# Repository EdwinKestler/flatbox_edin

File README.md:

# flatbox_edin
Remote math inclusive education for the vision impaired

This is our first attempt to bring remote math edcuation to vision impaired persons. 

#IoT to empower humans. 

Hardware: Raspberry pi 4, 4GB Gateway paired via Wifi to Haptic interfase (drv2603) with response mechanism (MAX6817 de bounce) (vibration motors and push buttons) 2 units. 
IoT: JSON, MQTT, WiFi.
Software: Rabbit MQ, Node-Red, Maria DB, Node.js Angular 9
Cloud: Goolge cloud-> BigQuery, Pub/Sub, Cloud Functions (python and Node.js) 

Main Idea: so a teacher can remotely teach math  to many vision imparied studentes. 1 to many or 1 to 1, via the internet and aremote conference call
Techers interface:

Basic Hardware interface:

Licencing:

Software: 

Hardware: License: <tspan y="0" x="71.357224" id="tspan1179">CERN-OHL-1.2</tspan></text></g></g><text id="text1788" y="-45.219803" x="138.91757" style="font-style:normal;font-weight:normal;font-size:40.0001px;line-height:1.25;font-family:sans-serif;fill:#000000;fill-opacity:1;stroke:none;stroke-width:1" xml:space="preserve">
  
Documentation:

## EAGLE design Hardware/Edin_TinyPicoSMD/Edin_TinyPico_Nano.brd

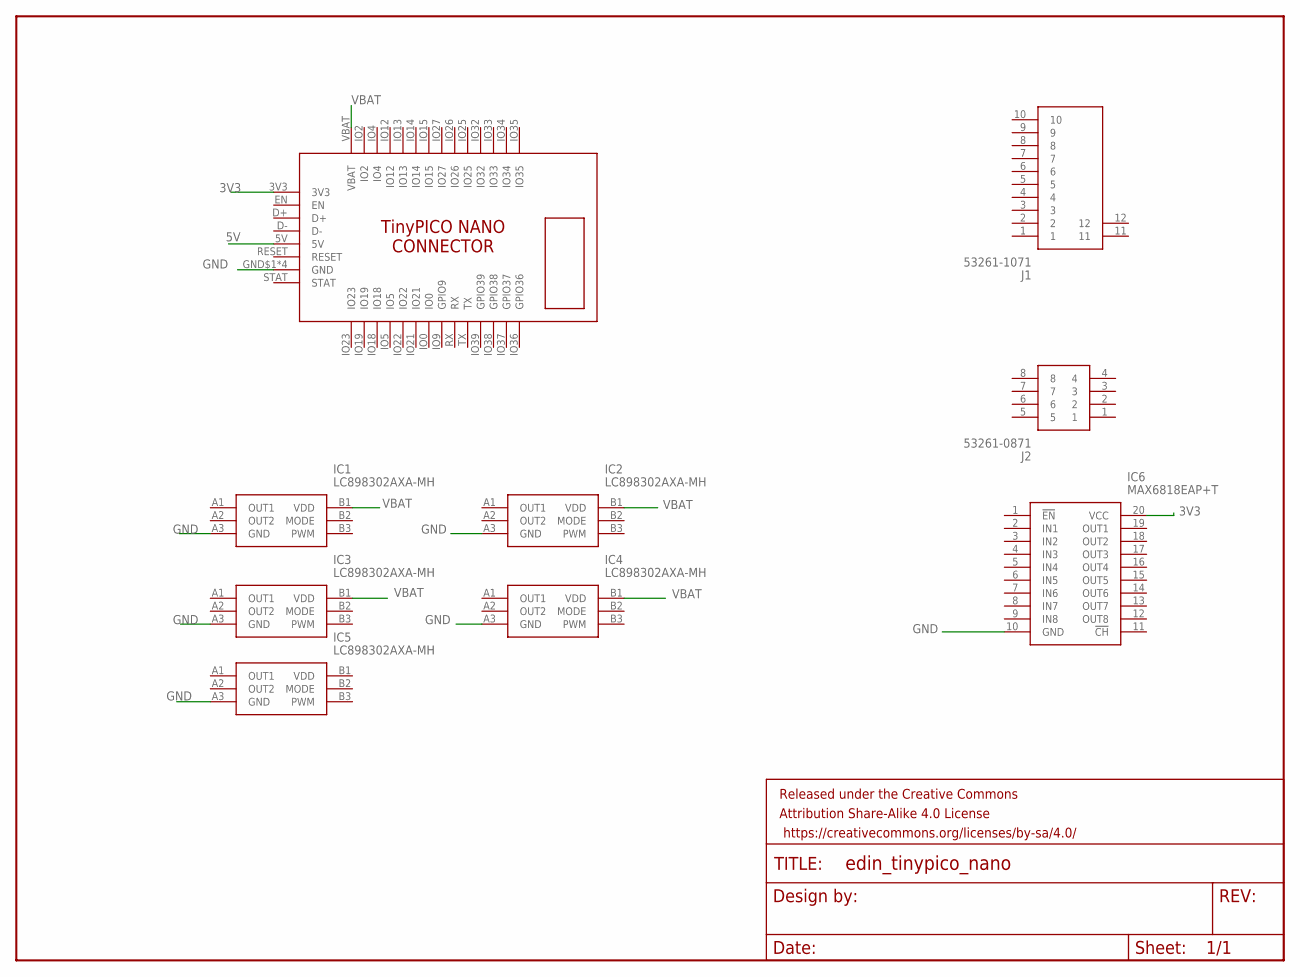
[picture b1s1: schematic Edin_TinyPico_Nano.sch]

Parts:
FRAME1: FRAME-LETTER; CREATIVE_COMMONS
IC1, IC2, IC3, IC4, IC5: LC898302AXA-MH; BGA6C40P3X2_118X78X65
IC6: MAX6818EAP+T; SOP65P778X199-20N
J1: 53261-1071; 532611071
J2: 53261-0871
U$1: TINYPICO-NANO-CONNECTOR

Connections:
3V3: IC6.20 (VCC), U$1.3V3
5V: U$1.5V
GND: IC1.A3 (GND), IC2.A3 (GND), IC3.A3 (GND), IC4.A3 (GND), IC5.A3 (GND), IC6.10 (GND), U$1.GND$1 (GND), U$1.GND$2 (GND), U$1.GND$3 (GND), U$1.GND$4 (GND)
VBAT: IC1.B1 (VDD), IC2.B1 (VDD), IC3.B1 (VDD), IC4.B1 (VDD), U$1.VBAT

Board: 2 copper layers, 10 parts (0 on the bottom side), 3 nets, no tracks yet.

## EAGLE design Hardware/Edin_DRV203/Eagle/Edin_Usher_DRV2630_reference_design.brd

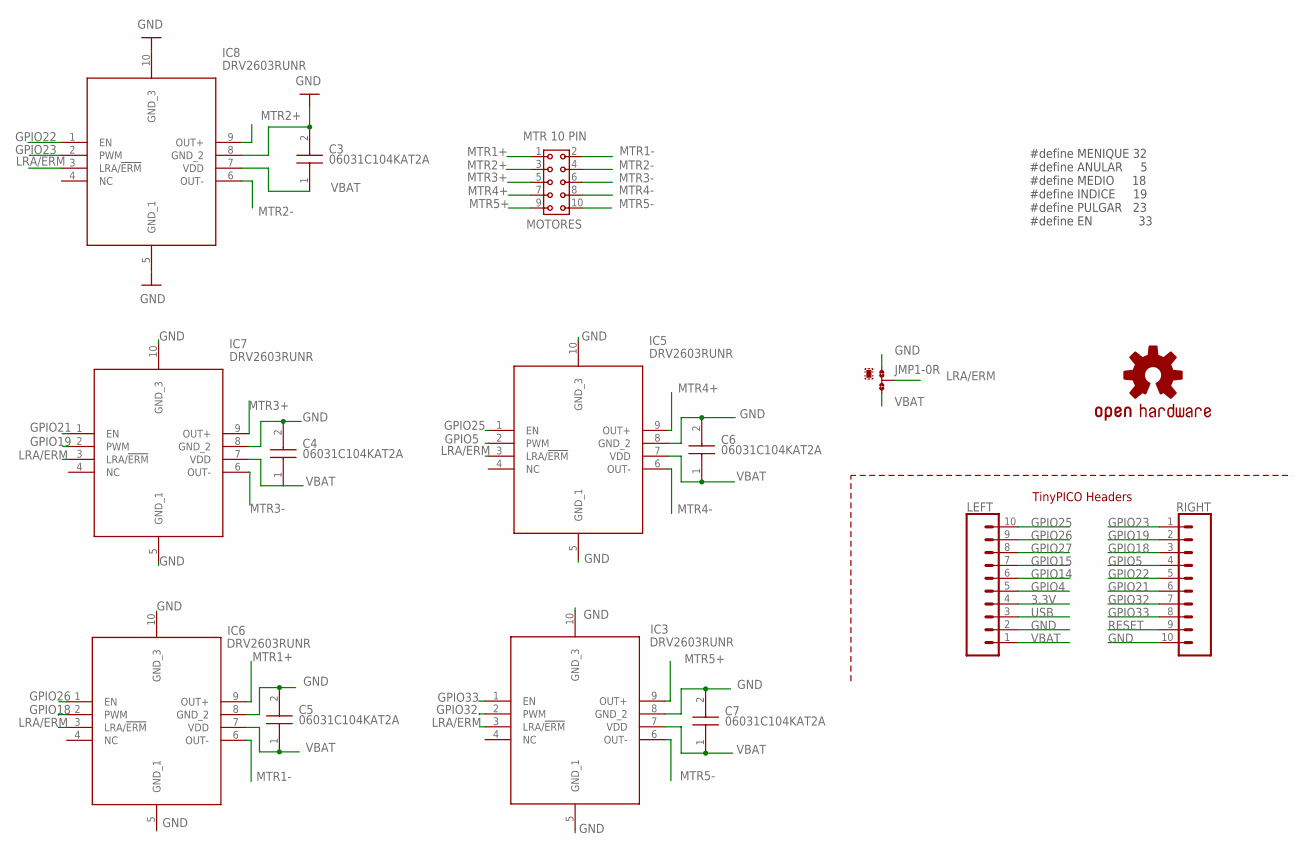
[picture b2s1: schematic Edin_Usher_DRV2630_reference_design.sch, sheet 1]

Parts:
C3, C4, C5, C6, C7: 06031C104KAT2A; CAPC1608X90N
IC3, IC5, IC6, IC7, IC8: DRV2603RUNR; QFN50P200X200X80-10N
JMP1: 0R-JUMPA; A0R-JMP
LEFT: TINYPICO_HEADER_10NO_SILK_PTH_FEMALE; 1X10_NO_SILK
LOGO1: OSHW-LOGOS; OSHW-LOGO-S
MOTORES: MTR 10 PIN; 61301021821
RIGHT: TINYPICO_HEADER_10NO_SILK_PTH_FEMALE; 1X10_NO_SILK

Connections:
3.3V: LEFT.4; also elsewhere on the board
GND: C3.2, C4.2, C5.2, C6.2, C7.2, IC3.5 (GND_1), IC3.8 (GND_2), IC3.10 (GND_3), IC5.5 (GND_1), IC5.8 (GND_2), IC5.10 (GND_3), IC6.5 (GND_1), IC6.8 (GND_2), IC6.10 (GND_3), IC7.5 (GND_1), IC7.8 (GND_2), IC7.10 (GND_3), IC8.5 (GND_1), IC8.8 (GND_2), IC8.10 (GND_3), JMP1.1, LEFT.2, RIGHT.10; also elsewhere on the board
GPIO4: LEFT.5; also elsewhere on the board
GPIO5: IC5.2 (PWM), RIGHT.4
GPIO14: LEFT.6; also elsewhere on the board
GPIO15: LEFT.7; also elsewhere on the board
GPIO18: IC6.2 (PWM), RIGHT.3
GPIO19: IC7.2 (PWM), RIGHT.2
GPIO21: IC7.1 (EN), RIGHT.6
GPIO22: IC8.1 (EN), RIGHT.5
GPIO23: IC8.2 (PWM), RIGHT.1
GPIO25: IC5.1 (EN), LEFT.10
GPIO26: IC6.1 (EN), LEFT.9
GPIO27: LEFT.8; also elsewhere on the board
GPIO32: IC3.2 (PWM), RIGHT.7
GPIO33: IC3.1 (EN), RIGHT.8
LRA/ERM: IC3.3 (LRA/!ERM), IC5.3 (LRA/!ERM), IC6.3 (LRA/!ERM), IC7.3 (LRA/!ERM), IC8.3 (LRA/!ERM), JMP1.2
MTR1+: IC6.9 (OUT+), MOTORES.1
MTR1-: IC6.6 (OUT-), MOTORES.2
MTR2+: IC8.9 (OUT+), MOTORES.3
MTR2-: IC8.6 (OUT-), MOTORES.4
MTR3+: IC7.9 (OUT+), MOTORES.5
MTR3-: IC7.6 (OUT-), MOTORES.6
MTR4+: IC5.9 (OUT+), MOTORES.7
MTR4-: IC5.6 (OUT-), MOTORES.8
MTR5+: IC3.9 (OUT+), MOTORES.9
MTR5-: IC3.6 (OUT-), MOTORES.10
RESET: RIGHT.9; also elsewhere on the board
USB: LEFT.3
VBAT: C3.1, C4.1, C5.1, C6.1, C7.1, IC3.7 (VDD), IC5.7 (VDD), IC6.7 (VDD), IC7.7 (VDD), IC8.7 (VDD), JMP1.3, LEFT.1

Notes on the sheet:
TinyPICO Headers
#define MENIQUE 32 #define ANULAR 5 #define MEDIO 18 #define INDICE 19 #define PULGAR 23 #define EN 33

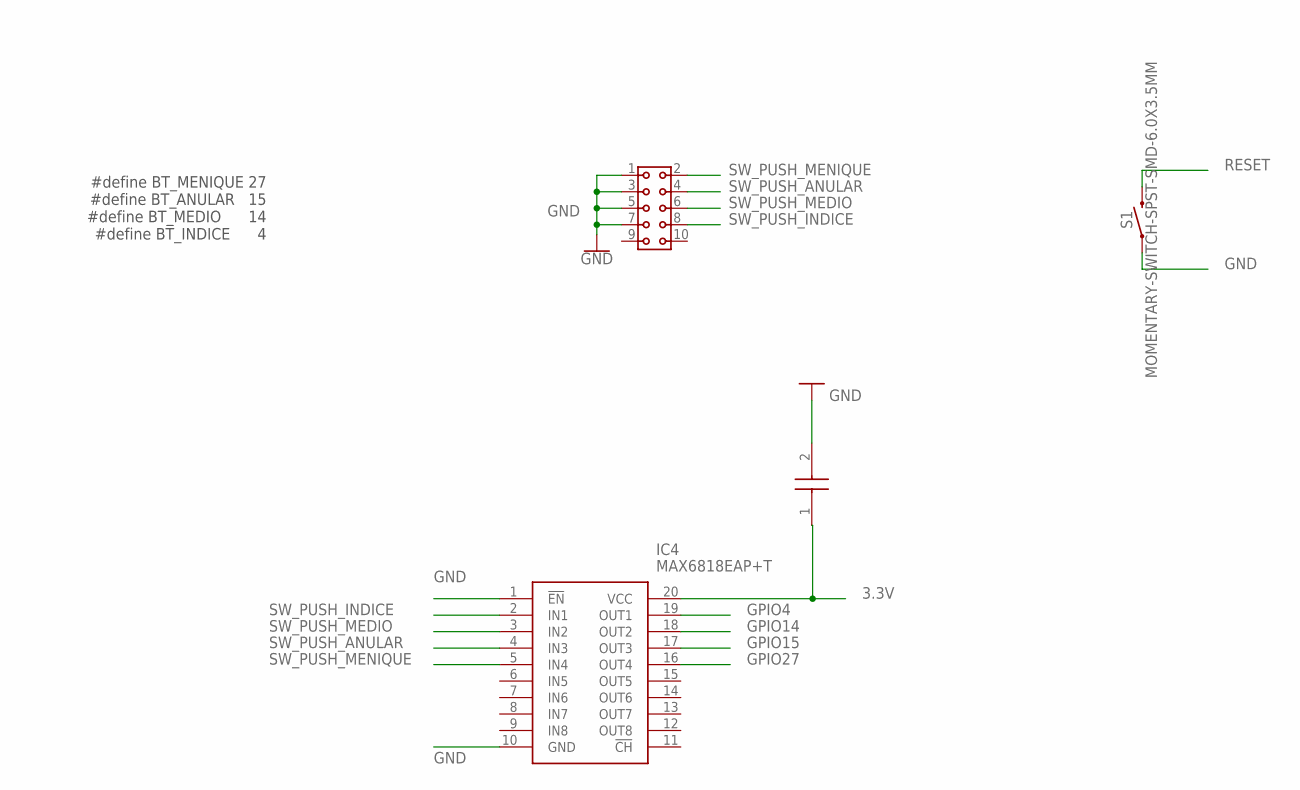
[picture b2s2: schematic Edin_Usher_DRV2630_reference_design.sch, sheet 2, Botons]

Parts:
BOTONES: BTN 10 PIN; 61301021821
C8: 0603B104K160CT; CAPC1608X87N
IC4: MAX6818EAP+T; SOP65P778X199-20N
S1: MOMENTARY-SWITCH-SPST-SMD-6.0X3.5MM; TACTILE_SWITCH_SMD_6.0X3.5MM

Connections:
3.3V: C8.1, IC4.20 (VCC); also elsewhere on the board
GND: BOTONES.1, BOTONES.3, BOTONES.5, BOTONES.7, C8.2, IC4.1 (!EN), IC4.10 (GND), S1.1; also elsewhere on the board
GPIO4: IC4.19 (OUT1); also elsewhere on the board
GPIO14: IC4.18 (OUT2); also elsewhere on the board
GPIO15: IC4.17 (OUT3); also elsewhere on the board
GPIO27: IC4.16 (OUT4); also elsewhere on the board
RESET: S1.2; also elsewhere on the board
SW_PUSH_ANULAR: BOTONES.4, IC4.4 (IN3)
SW_PUSH_INDICE: BOTONES.8, IC4.2 (IN1)
SW_PUSH_MEDIO: BOTONES.6, IC4.3 (IN2)
SW_PUSH_MENIQUE: BOTONES.2, IC4.5 (IN4)

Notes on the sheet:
#define BT_MENIQUE 27 #define BT_ANULAR 15 #define BT_MEDIO 14 #define BT_INDICE 4

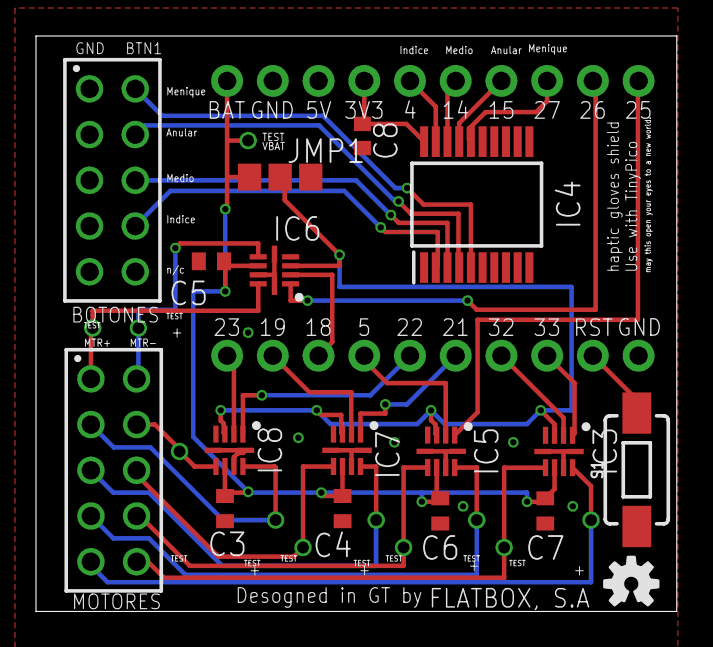
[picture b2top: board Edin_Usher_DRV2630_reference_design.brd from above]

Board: 2 copper layers, 35.6 x 32.0 mm, 20 parts (1 on the bottom side), 33 nets.

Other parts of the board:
LOGO2: OSHW-LOGOS; OSHW-LOGO-S

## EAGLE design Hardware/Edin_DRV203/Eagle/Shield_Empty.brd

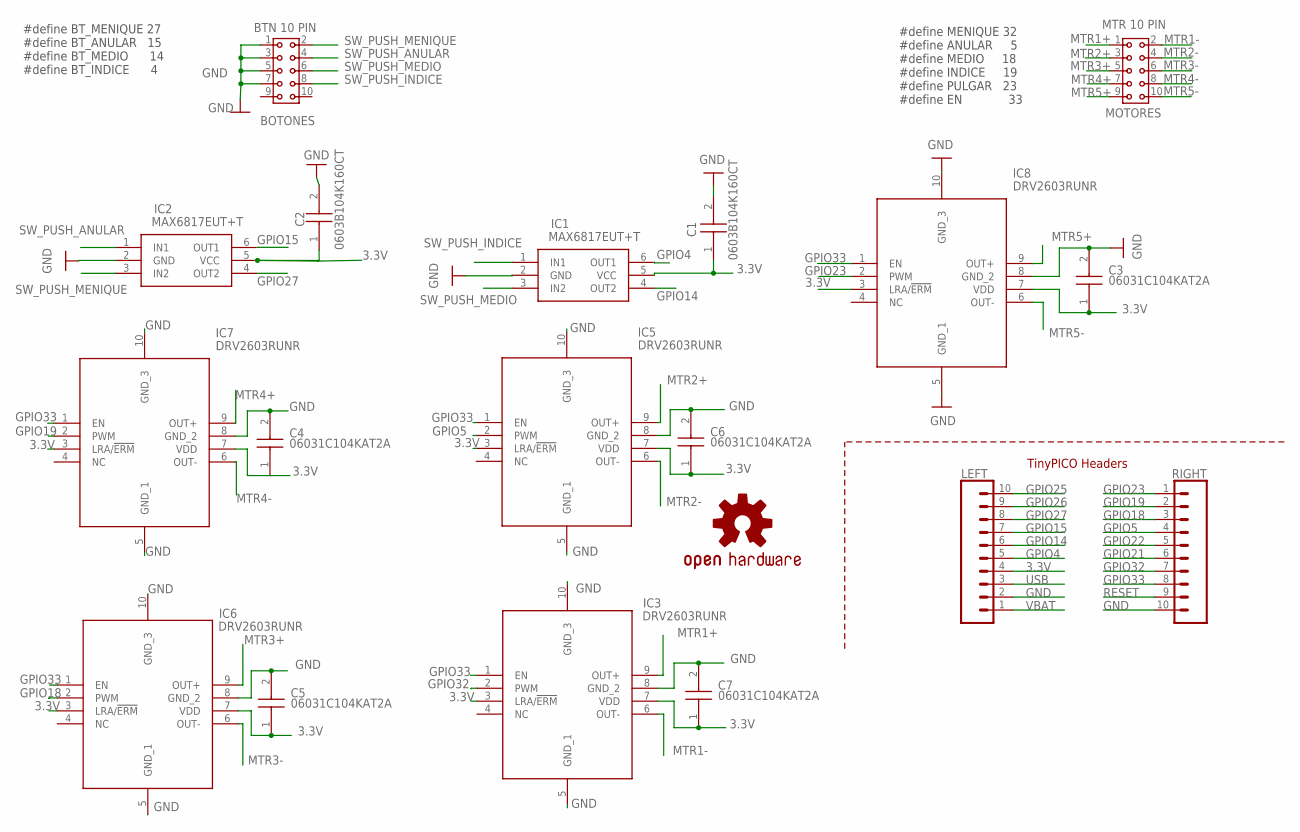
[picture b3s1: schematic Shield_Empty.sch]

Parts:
BOTONES: BTN 10 PIN; 61301021821
C1, C2: 0603B104K160CT; CAPC1608X87N
C3, C4, C5, C6, C7: 06031C104KAT2A; CAPC1608X90N
IC1, IC2: MAX6817EUT+T; SOT95P280X145-6N
IC3, IC5, IC6, IC7, IC8: DRV2603RUNR; QFN50P200X200X80-10N
LEFT: TINYPICO_HEADER_10NO_SILK_PTH_FEMALE; 1X10_NO_SILK
LOGO1: OSHW-LOGOS; OSHW-LOGO-S
MOTORES: MTR 10 PIN; 61301021821
RIGHT: TINYPICO_HEADER_10NO_SILK_PTH_FEMALE; 1X10_NO_SILK

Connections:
3.3V: C1.1, C2.1, C3.1, C4.1, C5.1, C6.1, C7.1, IC1.5 (VCC), IC2.5 (VCC), IC3.3 (LRA/!ERM), IC3.7 (VDD), IC5.3 (LRA/!ERM), IC5.7 (VDD), IC6.3 (LRA/!ERM), IC6.7 (VDD), IC7.3 (LRA/!ERM), IC7.7 (VDD), IC8.3 (LRA/!ERM), IC8.7 (VDD), LEFT.4
GND: BOTONES.1, BOTONES.3, BOTONES.5, BOTONES.7, C1.2, C2.2, C3.2, C4.2, C5.2, C6.2, C7.2, IC1.2 (GND), IC2.2 (GND), IC3.5 (GND_1), IC3.8 (GND_2), IC3.10 (GND_3), IC5.5 (GND_1), IC5.8 (GND_2), IC5.10 (GND_3), IC6.5 (GND_1), IC6.8 (GND_2), IC6.10 (GND_3), IC7.5 (GND_1), IC7.8 (GND_2), IC7.10 (GND_3), IC8.5 (GND_1), IC8.8 (GND_2), IC8.10 (GND_3), LEFT.2, RIGHT.10
GPIO4: IC1.6 (OUT1), LEFT.5
GPIO5: IC5.2 (PWM), RIGHT.4
GPIO14: IC1.4 (OUT2), LEFT.6
GPIO15: IC2.6 (OUT1), LEFT.7
GPIO18: IC6.2 (PWM), RIGHT.3
GPIO19: IC7.2 (PWM), RIGHT.2
GPIO21: RIGHT.6
GPIO22: RIGHT.5
GPIO23: IC8.2 (PWM), RIGHT.1
GPIO25: LEFT.10
GPIO26: LEFT.9
GPIO27: IC2.4 (OUT2), LEFT.8
GPIO32: IC3.2 (PWM), RIGHT.7
GPIO33: IC3.1 (EN), IC5.1 (EN), IC6.1 (EN), IC7.1 (EN), IC8.1 (EN), RIGHT.8
MTR1+: IC3.9 (OUT+), MOTORES.1
MTR1-: IC3.6 (OUT-), MOTORES.2
MTR2+: IC5.9 (OUT+), MOTORES.3
MTR2-: IC5.6 (OUT-), MOTORES.4
MTR3+: IC6.9 (OUT+), MOTORES.5
MTR3-: IC6.6 (OUT-), MOTORES.6
MTR4+: IC7.9 (OUT+), MOTORES.7
MTR4-: IC7.6 (OUT-), MOTORES.8
MTR5+: IC8.9 (OUT+), MOTORES.9
MTR5-: IC8.6 (OUT-), MOTORES.10
RESET: RIGHT.9
SW_PUSH_ANULAR: BOTONES.4, IC2.1 (IN1)
SW_PUSH_INDICE: BOTONES.8, IC1.1 (IN1)
SW_PUSH_MEDIO: BOTONES.6, IC1.3 (IN2)
SW_PUSH_MENIQUE: BOTONES.2, IC2.3 (IN2)
USB: LEFT.3
VBAT: LEFT.1

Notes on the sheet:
TinyPICO Headers
#define MENIQUE 32 #define ANULAR 5 #define MEDIO 18 #define INDICE 19 #define PULGAR 23 #define EN 33
#define BT_MENIQUE 27 #define BT_ANULAR 15 #define BT_MEDIO 14 #define BT_INDICE 4

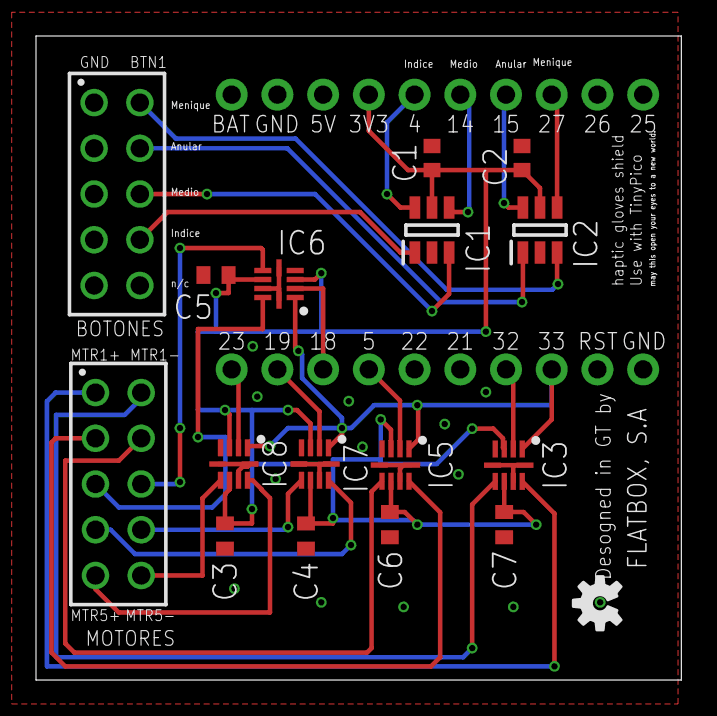
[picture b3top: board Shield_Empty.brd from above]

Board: 2 copper layers, 35.9 x 35.8 mm, 20 parts (1 on the bottom side), 26 nets.

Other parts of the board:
LOGO2: OSHW-LOGOS; OSHW-LOGO-S

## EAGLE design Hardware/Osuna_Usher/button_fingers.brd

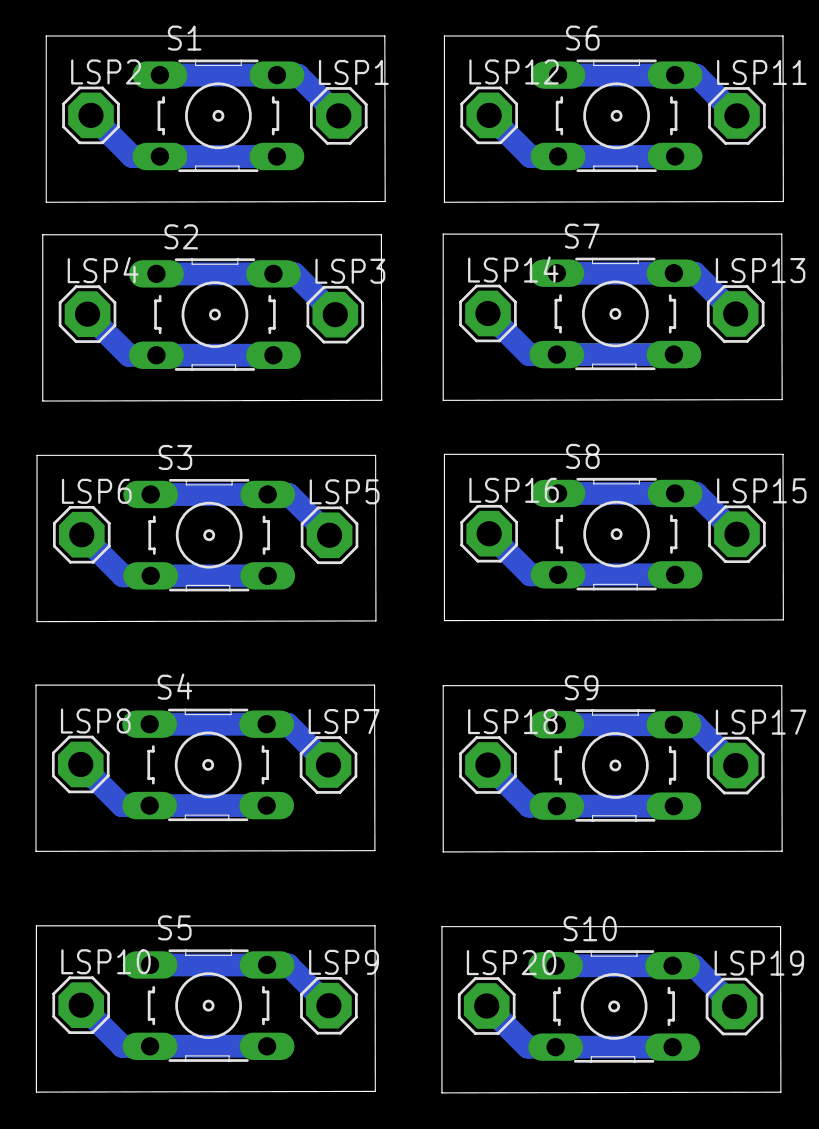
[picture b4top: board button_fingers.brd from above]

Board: 2 copper layers, 41.5 x 58.7 mm, 30 parts (0 on the bottom side), 20 nets.

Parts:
LSP1, LSP2, LSP3, LSP4, LSP5, LSP6, LSP7, LSP8, LSP9, LSP10, LSP11, LSP12, LSP13, LSP14, LSP15, LSP16, LSP17, LSP18, LSP19, LSP20: SE14
S1, S2, S3, S4, S5, S6, S7, S8, S9, S10: B3F-10XX

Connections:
unnamed: LSP1.MP, S1.1, S1.2
unnamed: LSP2.MP, S1.3, S1.4
unnamed: LSP3.MP, S2.1, S2.2
unnamed: LSP4.MP, S2.3, S2.4
unnamed: LSP5.MP, S3.1, S3.2
unnamed: LSP6.MP, S3.3, S3.4
unnamed: LSP7.MP, S4.1, S4.2
unnamed: LSP8.MP, S4.3, S4.4
unnamed: LSP9.MP, S5.1, S5.2
unnamed: LSP10.MP, S5.3, S5.4
unnamed: LSP11.MP, S6.1, S6.2
unnamed: LSP12.MP, S6.3, S6.4
unnamed: LSP13.MP, S7.1, S7.2
unnamed: LSP14.MP, S7.3, S7.4
unnamed: LSP15.MP, S8.1, S8.2
unnamed: LSP16.MP, S8.3, S8.4
unnamed: LSP17.MP, S9.1, S9.2
unnamed: LSP18.MP, S9.3, S9.4
unnamed: LSP19.MP, S10.1, S10.2
unnamed: LSP20.MP, S10.3, S10.4

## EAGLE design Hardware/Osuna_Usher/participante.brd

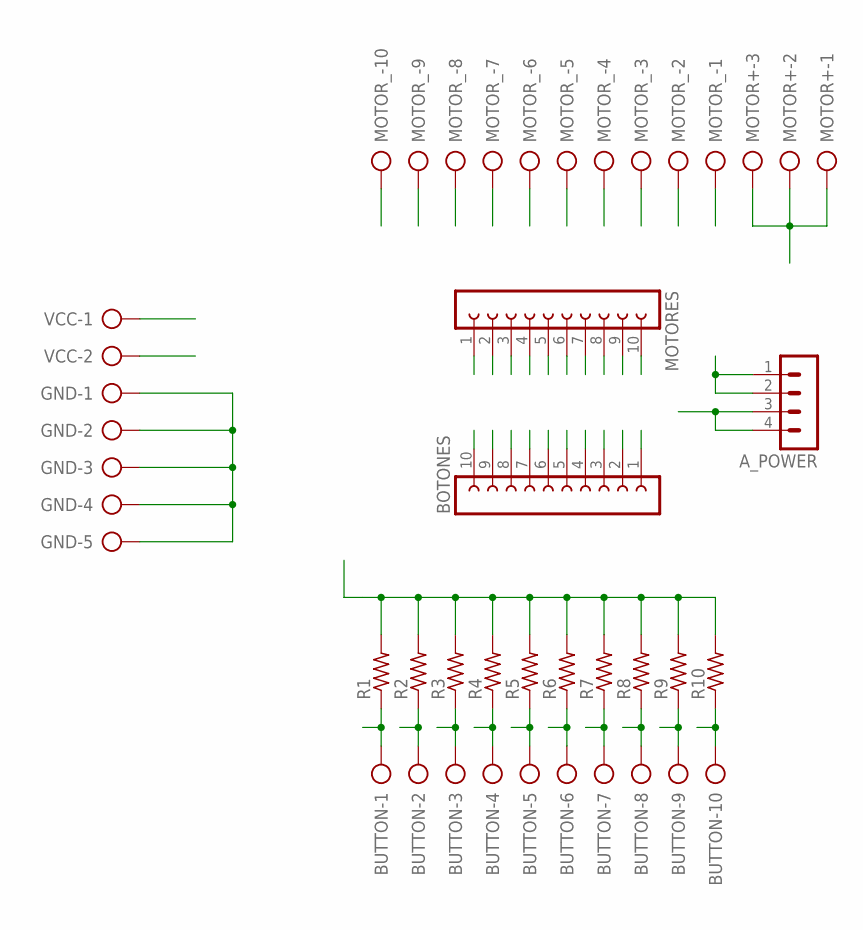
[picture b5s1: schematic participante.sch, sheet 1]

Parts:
A_POWER: MA04-1
BOTONES: FE10-1; FE10
BUTTON: AK300/10
GND: AK300/5
MOTOR+: AK300/3
MOTORES: FE10-1; FE10
MOTOR_: AK300/10
R1, R2, R3, R4, R5, R6, R7, R8, R9, R10: R-US_0204/7; 0204/7
VCC: AK300/2

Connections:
5VDC: R1.2, R2.2, R3.2, R4.2, R5.2, R6.2, R7.2, R8.2, R9.2, R10.2; also elsewhere on the board
A22: BOTONES.1, BUTTON.1, R1.1
A23: BOTONES.2, BUTTON.2, R2.1
A24: BOTONES.3, BUTTON.3, R3.1
A25: BOTONES.4, BUTTON.4, R4.1
A26: BOTONES.5, BUTTON.5, R5.1
A27: BOTONES.6, BUTTON.6, R6.1
A28: BOTONES.7, BUTTON.7, R7.1
A29: BOTONES.8, BUTTON.8, R8.1
A30: BOTONES.9, BUTTON.9, R9.1
A31: BOTONES.10, BUTTON.10, R10.1
AM_1: MOTORES.1; also elsewhere on the board
AM_2: MOTORES.2; also elsewhere on the board
AM_3: MOTORES.3; also elsewhere on the board
AM_4: MOTORES.4; also elsewhere on the board
AM_5: MOTORES.5; also elsewhere on the board
AM_6: MOTORES.6; also elsewhere on the board
AM_7: MOTORES.7; also elsewhere on the board
AM_8: MOTORES.8; also elsewhere on the board
AM_9: MOTORES.9; also elsewhere on the board
AM_10: MOTORES.10; also elsewhere on the board
GND: A_POWER.1, A_POWER.2, GND.1, GND.2, GND.3, GND.4, GND.5; also elsewhere on the board
M_N1: MOTOR_.1; also elsewhere on the board
M_N2: MOTOR_.2; also elsewhere on the board
M_N3: MOTOR_.3; also elsewhere on the board
M_N4: MOTOR_.4; also elsewhere on the board
M_N5: MOTOR_.5; also elsewhere on the board
M_N6: MOTOR_.6; also elsewhere on the board
M_N7: MOTOR_.7; also elsewhere on the board
M_N8: MOTOR_.8; also elsewhere on the board
M_N9: MOTOR_.9; also elsewhere on the board
M_N10: MOTOR_.10; also elsewhere on the board
VCC: MOTOR+.1, MOTOR+.2, MOTOR+.3, VCC.2; also elsewhere on the board
VCC_A: A_POWER.3, A_POWER.4, VCC.1

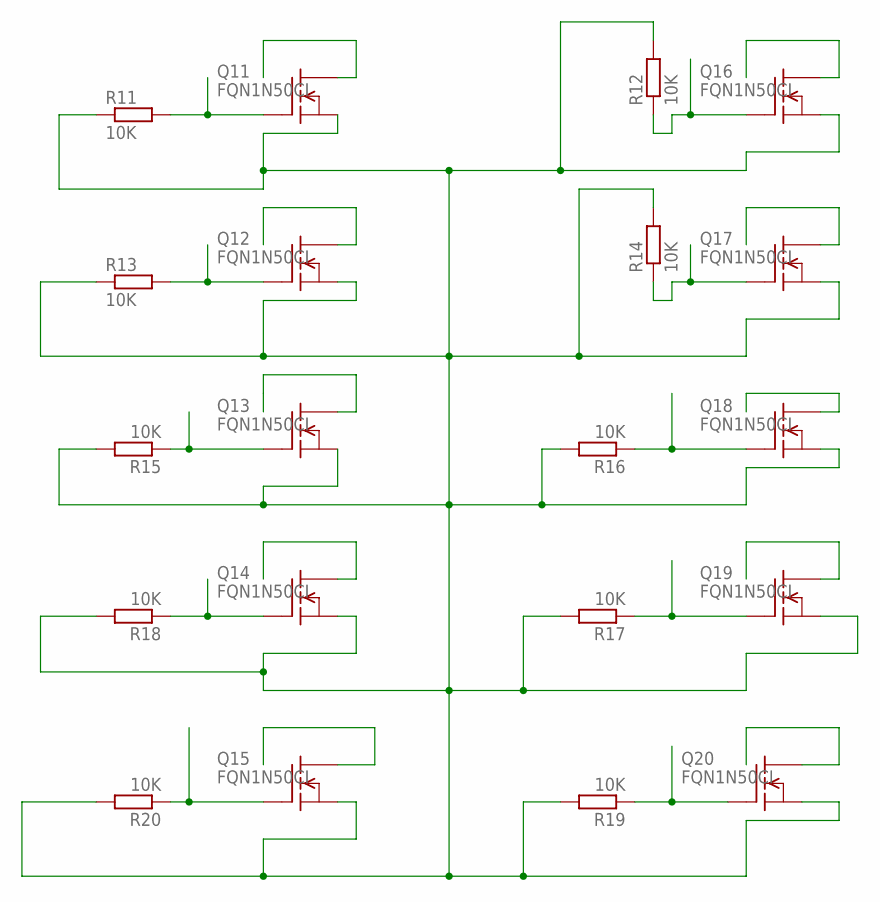
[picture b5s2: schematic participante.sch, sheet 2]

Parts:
Q11, Q12, Q13, Q14, Q15, Q16, Q17, Q18, Q19, Q20: FQN1N50CI; TO92-INLINE
R11, R12, R13, R14, R15, R16, R17, R18, R19, R20: 10K; 0207/10

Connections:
AM_1: Q11.2 (G), R11.2; also elsewhere on the board
AM_2: Q12.2 (G), R13.2; also elsewhere on the board
AM_3: Q13.2 (G), R15.1; also elsewhere on the board
AM_4: Q14.2 (G), R18.1; also elsewhere on the board
AM_5: Q15.2 (G), R20.1; also elsewhere on the board
AM_6: Q20.2 (G), R19.1; also elsewhere on the board
AM_7: Q19.2 (G), R17.1; also elsewhere on the board
AM_8: Q18.2 (G), R16.1; also elsewhere on the board
AM_9: Q17.2 (G), R14.1; also elsewhere on the board
AM_10: Q16.2 (G), R12.1; also elsewhere on the board
GND: Q11.3 (S), Q12.3 (S), Q13.3 (S), Q14.3 (S), Q15.3 (S), Q16.3 (S), Q17.3 (S), Q18.3 (S), Q19.3 (S), Q20.3 (S), R11.1, R12.2, R13.1, R14.2, R15.2, R16.2, R17.2, R18.2, R19.2, R20.2; also elsewhere on the board
M_N1: Q11.1 (D); also elsewhere on the board
M_N2: Q12.1 (D); also elsewhere on the board
M_N3: Q13.1 (D); also elsewhere on the board
M_N4: Q14.1 (D); also elsewhere on the board
M_N5: Q15.1 (D); also elsewhere on the board
M_N6: Q16.1 (D); also elsewhere on the board
M_N7: Q17.1 (D); also elsewhere on the board
M_N8: Q18.1 (D); also elsewhere on the board
M_N9: Q19.1 (D); also elsewhere on the board
M_N10: Q20.1 (D); also elsewhere on the board

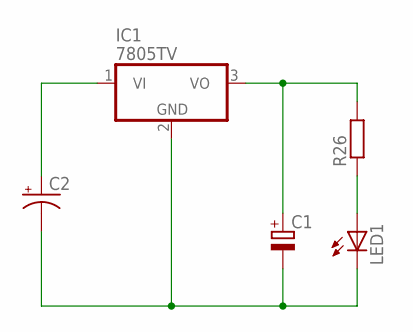
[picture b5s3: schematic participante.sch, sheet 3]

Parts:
C1: CPOL-EUE2.5-6; E2,5-6
C2: CPOL-USE3.5-8; E3,5-8
IC1: 7805TV; TO220V
LED1: LED5MM
R26: R-EU_0207/10; 0207/10

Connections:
5VDC: C1.+, IC1.3 (VO), R26.2; also elsewhere on the board
GND: C1.-, C2.-, IC1.2 (GND), LED1.K (C); also elsewhere on the board
unnamed: LED1.A, R26.1
VCC: C2.+, IC1.1 (VI); also elsewhere on the board

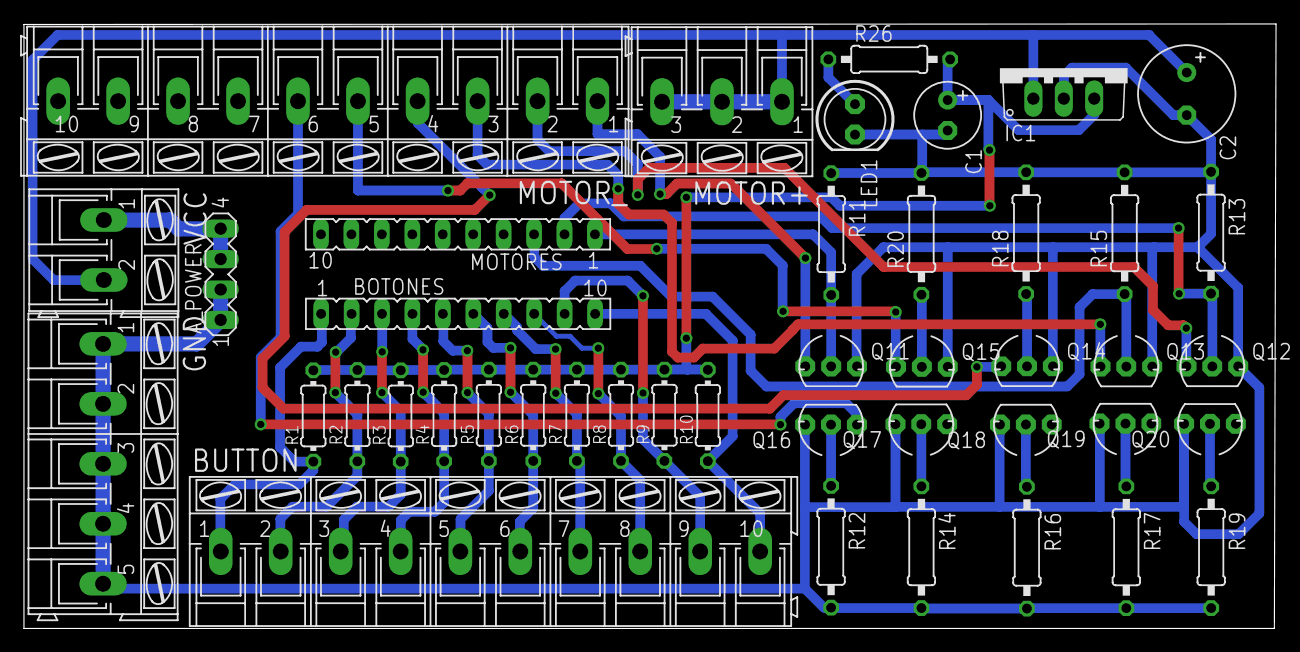
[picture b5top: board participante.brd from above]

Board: 2 copper layers, 104.5 x 50.4 mm, 43 parts (0 on the bottom side), 35 nets.

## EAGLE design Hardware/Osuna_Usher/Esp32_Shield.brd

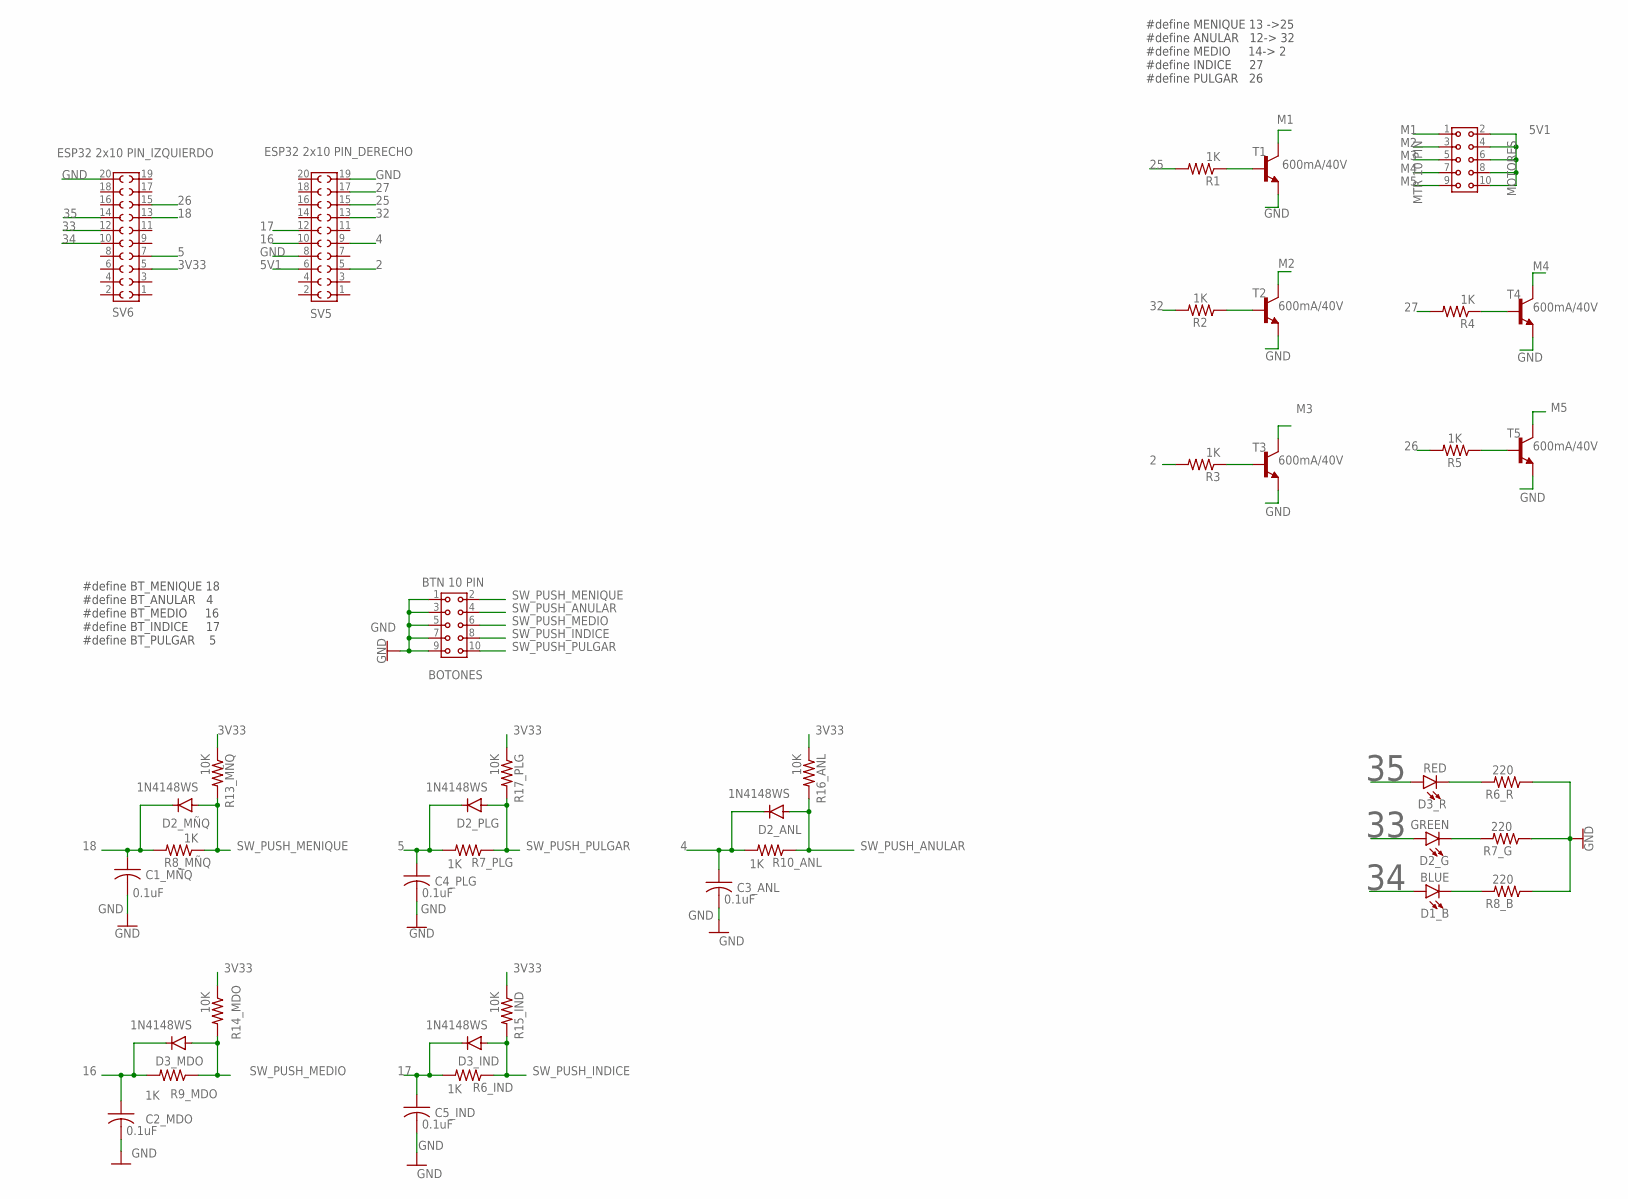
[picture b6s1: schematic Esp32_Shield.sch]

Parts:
BOTONES: BTN 10 PIN; 61301021821
C1_MÑQ, C2_MDO, C3_ANL, C4_PLG, C5_IND: 0.1uF; C0805
D1_B: BLUE; LED-1206
D2_ANL, D2_MÑQ, D2_PLG, D3_IND, D3_MDO: 1N4148WS; SOD-323
D2_G: GREEN; LED-1206
D3_R: RED; LED-1206
MOTORES: MTR 10 PIN; 61301021821
R1, R2, R3, R4, R5, R6_IND, R7_PLG, R8_MÑQ, R9_MDO, R10_ANL: 1K; R0805
R6_R, R7_G, R8_B: 220; R0805
R13_MÑQ, R14_MDO, R15_IND, R16_ANL, R17_PLG: 10K; R0805
SV5: ESP32 2x10 PIN_DERECHO; 61302021821
SV6: ESP32 2x10 PIN_IZQUIERDO; 61302021821
T1, T2, T3, T4, T5: 600mA/40V; SOT23-3

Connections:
2: R3.2, SV5.5
3V33: R13_MÑQ.1, R14_MDO.1, R15_IND.1, R16_ANL.1, R17_PLG.1, SV6.5
4: C3_ANL.1, D2_ANL.C, R10_ANL.2, SV5.9
5: C4_PLG.1, D2_PLG.C, R7_PLG.2, SV6.7
5V1: MOTORES.2, MOTORES.4, MOTORES.6, MOTORES.8, MOTORES.10, SV5.6
16: C2_MDO.1, D3_MDO.C, R9_MDO.2, SV5.10
17: C5_IND.1, D3_IND.C, R6_IND.2, SV5.12
18: C1_MÑQ.1, D2_MÑQ.C, R8_MÑQ.2, SV6.13
25: R1.2, SV5.15
26: R5.2, SV6.15
27: R4.2, SV5.17
32: R2.2, SV5.13
33: D2_G.A, SV6.12
34: D1_B.A, SV6.10
35: D3_R.A, SV6.14
GND: BOTONES.1, BOTONES.3, BOTONES.5, BOTONES.7, BOTONES.9, C1_MÑQ.2, C2_MDO.2, C3_ANL.2, C4_PLG.2, C5_IND.2, R6_R.1, R7_G.1, R8_B.1, SV5.8, SV5.19, SV6.20, T1.2 (E), T2.2 (E), T3.2 (E), T4.2 (E), T5.2 (E)
M1: MOTORES.1, T1.3 (C)
M2: MOTORES.3, T2.3 (C)
M3: MOTORES.5, T3.3 (C)
M4: MOTORES.7, T4.3 (C)
M5: MOTORES.9, T5.3 (C)
unnamed: R2.1, T2.1 (B)
unnamed: R1.1, T1.1 (B)
unnamed: R3.1, T3.1 (B)
unnamed: D3_R.C, R6_R.2
unnamed: D2_G.C, R7_G.2
unnamed: D1_B.C, R8_B.2
unnamed: R4.1, T4.1 (B)
unnamed: R5.1, T5.1 (B)
SW_PUSH_ANULAR: BOTONES.4, D2_ANL.A, R10_ANL.1, R16_ANL.2
SW_PUSH_INDICE: BOTONES.8, D3_IND.A, R6_IND.1, R15_IND.2
SW_PUSH_MEDIO: BOTONES.6, D3_MDO.A, R9_MDO.1, R14_MDO.2
SW_PUSH_MENIQUE: BOTONES.2, D2_MÑQ.A, R8_MÑQ.1, R13_MÑQ.2
SW_PUSH_PULGAR: BOTONES.10, D2_PLG.A, R7_PLG.1, R17_PLG.2

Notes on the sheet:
#define MENIQUE 13 ->25 #define ANULAR 12-> 32 #define MEDIO 14-> 2 #define INDICE 27 #define PULGAR 26
#define BT_MENIQUE 18 #define BT_ANULAR 4 #define BT_MEDIO 16 #define BT_INDICE 17 #define BT_PULGAR 5

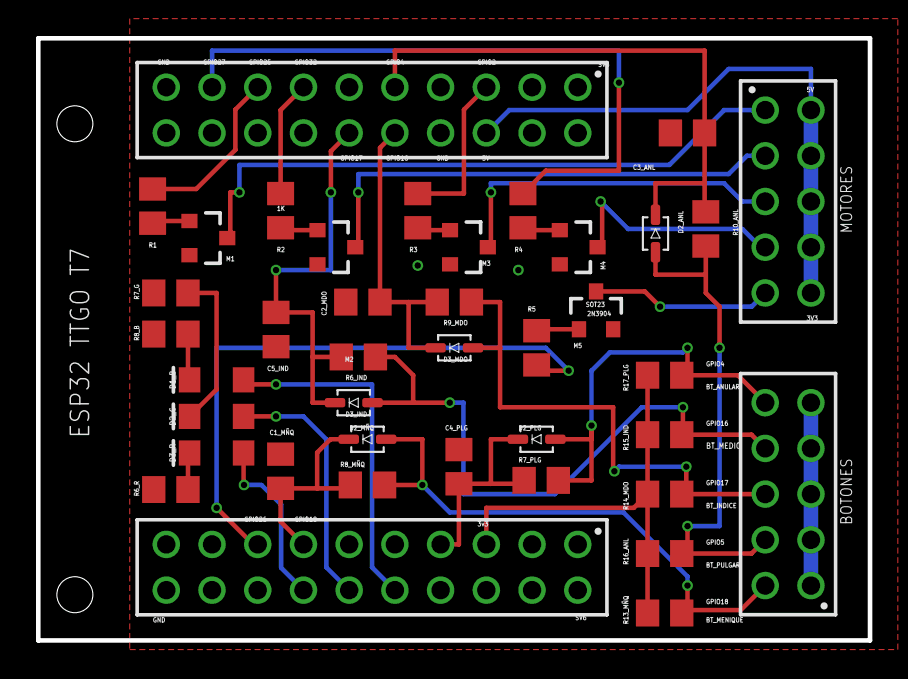
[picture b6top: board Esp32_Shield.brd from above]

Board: 2 copper layers, 46.2 x 33.5 mm, 40 parts (0 on the bottom side), 34 nets.

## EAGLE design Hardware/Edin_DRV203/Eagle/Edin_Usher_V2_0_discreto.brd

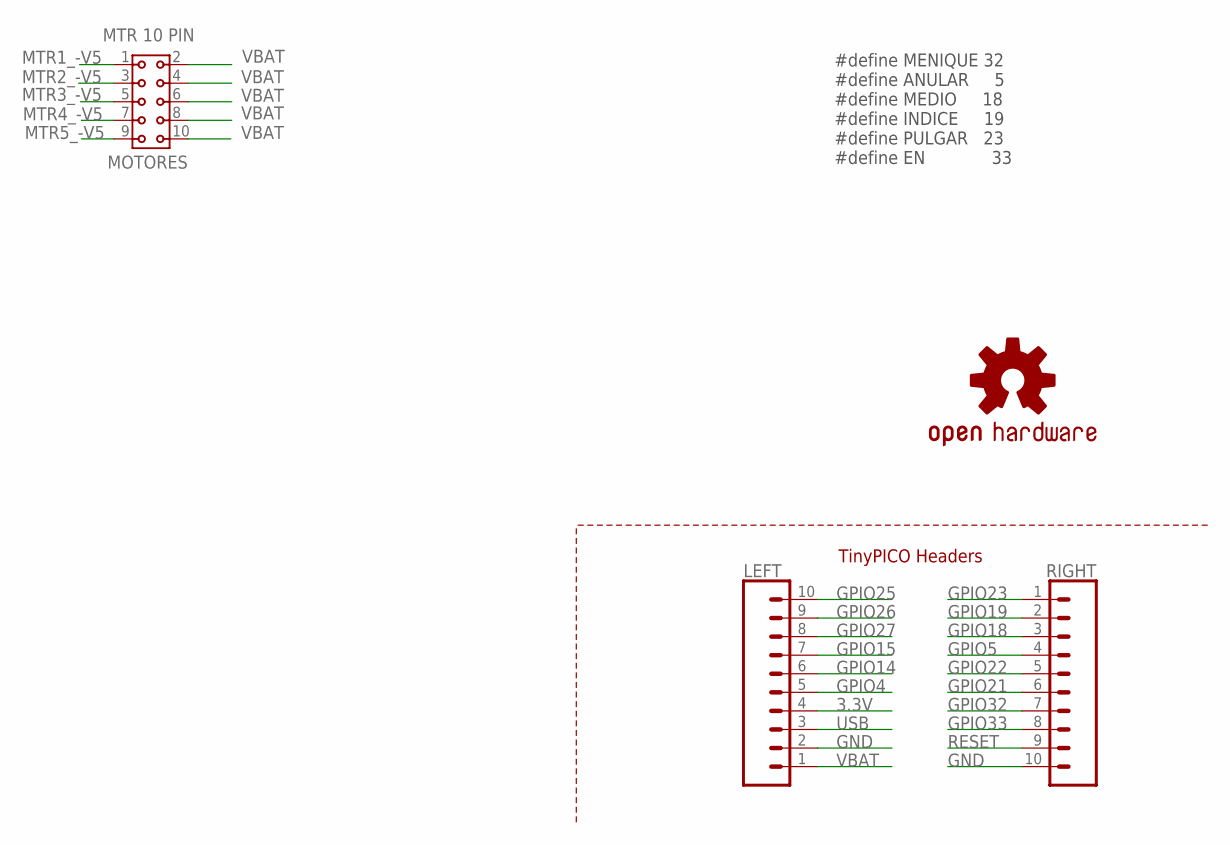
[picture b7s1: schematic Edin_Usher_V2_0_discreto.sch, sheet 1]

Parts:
LEFT: TINYPICO_HEADER_10NO_SILK_PTH_FEMALE; 1X10_NO_SILK
LOGO1: OSHW-LOGOS; OSHW-LOGO-S
MOTORES: MTR 10 PIN; 61301021821
RIGHT: TINYPICO_HEADER_10NO_SILK_PTH_FEMALE; 1X10_NO_SILK

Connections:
3.3V: LEFT.4; also elsewhere on the board
GND: LEFT.2, RIGHT.10; also elsewhere on the board
GPIO4: LEFT.5; also elsewhere on the board
GPIO5: RIGHT.4
GPIO14: LEFT.6; also elsewhere on the board
GPIO15: LEFT.7; also elsewhere on the board
GPIO18: RIGHT.3; also elsewhere on the board
GPIO19: RIGHT.2; also elsewhere on the board
GPIO21: RIGHT.6; also elsewhere on the board
GPIO22: RIGHT.5; also elsewhere on the board
GPIO23: RIGHT.1; also elsewhere on the board
GPIO25: LEFT.10
GPIO26: LEFT.9
GPIO27: LEFT.8; also elsewhere on the board
GPIO32: RIGHT.7
GPIO33: RIGHT.8
MTR1_-V5: MOTORES.1; also elsewhere on the board
MTR2_-V5: MOTORES.3; also elsewhere on the board
MTR3_-V5: MOTORES.5; also elsewhere on the board
MTR4_-V5: MOTORES.7; also elsewhere on the board
MTR5_-V5: MOTORES.9; also elsewhere on the board
RESET: RIGHT.9; also elsewhere on the board
USB: LEFT.3
VBAT: LEFT.1, MOTORES.2, MOTORES.4, MOTORES.6, MOTORES.8, MOTORES.10

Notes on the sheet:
TinyPICO Headers
#define MENIQUE 32 #define ANULAR 5 #define MEDIO 18 #define INDICE 19 #define PULGAR 23 #define EN 33

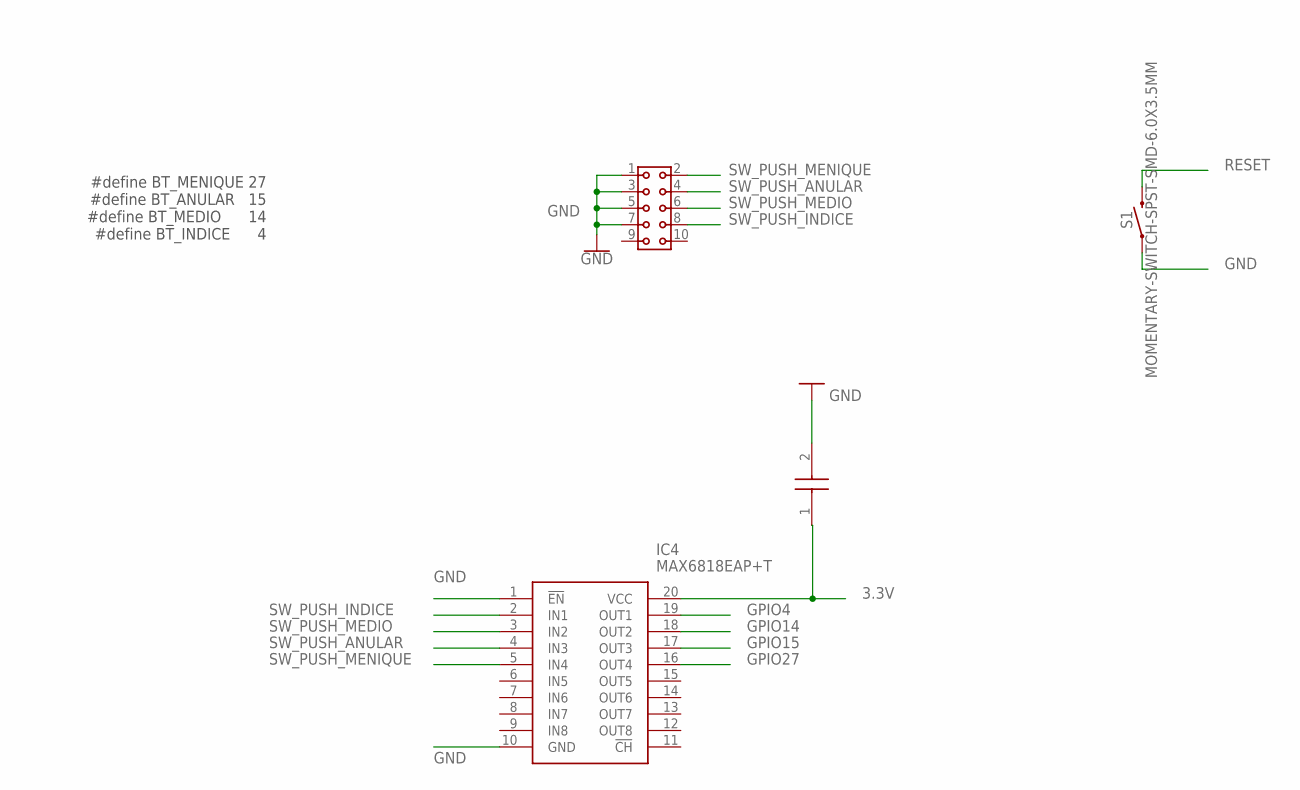
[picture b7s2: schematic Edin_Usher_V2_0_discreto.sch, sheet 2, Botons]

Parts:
BOTONES: BTN 10 PIN; 61301021821
C8: 0603B104K160CT; CAPC1608X87N
IC4: MAX6818EAP+T; SOP65P778X199-20N
S1: MOMENTARY-SWITCH-SPST-SMD-6.0X3.5MM; TACTILE_SWITCH_SMD_6.0X3.5MM

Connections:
3.3V: C8.1, IC4.20 (VCC); also elsewhere on the board
GND: BOTONES.1, BOTONES.3, BOTONES.5, BOTONES.7, C8.2, IC4.1 (!EN), IC4.10 (GND), S1.1; also elsewhere on the board
GPIO4: IC4.19 (OUT1); also elsewhere on the board
GPIO14: IC4.18 (OUT2); also elsewhere on the board
GPIO15: IC4.17 (OUT3); also elsewhere on the board
GPIO27: IC4.16 (OUT4); also elsewhere on the board
RESET: S1.2; also elsewhere on the board
SW_PUSH_ANULAR: BOTONES.4, IC4.4 (IN3)
SW_PUSH_INDICE: BOTONES.8, IC4.2 (IN1)
SW_PUSH_MEDIO: BOTONES.6, IC4.3 (IN2)
SW_PUSH_MENIQUE: BOTONES.2, IC4.5 (IN4)

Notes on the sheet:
#define BT_MENIQUE 27 #define BT_ANULAR 15 #define BT_MEDIO 14 #define BT_INDICE 4

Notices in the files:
README.md:
License: MIT
License: CC BY-SA 4.0
parts and their libraries:
SparkFun-Aesthetics: Licensing: Creative Commons ShareAlike 4.0 International - https://creativecommons.org/licenses/by-sa/4.0
Wurth_Connectors_WR-PHD: Copyright: Würth Elektronik
SparkFun-Aesthetics: Released under the Creative Commons Attribution Share-Alike 4.0 License
